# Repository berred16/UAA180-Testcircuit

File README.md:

# UAA180-Testcircuit
Cascading UAA180
Here you can find a drawing of the UAA180 Levelmeter in a single circuit as well as in cascading structure

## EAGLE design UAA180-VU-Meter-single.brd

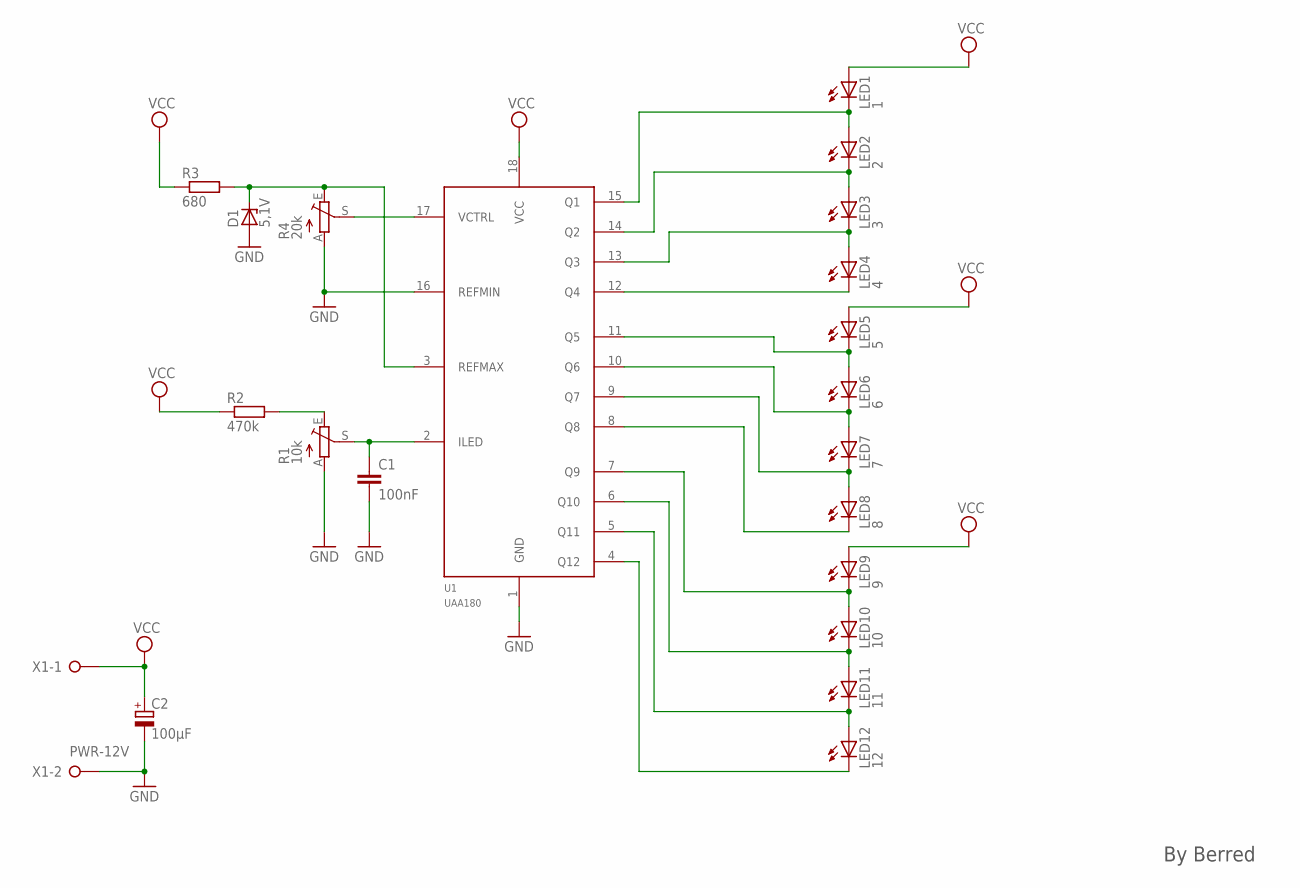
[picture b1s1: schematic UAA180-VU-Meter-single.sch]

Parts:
C1: 100nF; C025-024X044
C2: 100µF; E2,5-7
D1: 5,1V; DO35Z10
LED1: 1; LED2X5
LED2: 2; LED2X5
LED3: 3; LED2X5
LED4: 4; LED2X5
LED5: 5; LED2X5
LED6: 6; LED2X5
LED7: 7; LED2X5
LED8: 8; LED2X5
LED9: 9; LED2X5
LED10: 10; LED2X5
LED11: 11; LED2X5
LED12: 12; LED2X5
R1: 10k; B25P
R2: 470k; 0207/10
R3: 680; 0207/10
R4: 20k; B25P
U1: UAA180; DIL18
X1: PWR-12V; W237-132

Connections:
GND: C1.2, C2.-, D1.A, R1.A, R4.A, U1.1 (GND), U1.16 (REFMIN), X1.2
unnamed: LED1.K (C), LED2.A, U1.15 (Q1)
unnamed: LED2.K (C), LED3.A, U1.14 (Q2)
unnamed: LED3.K (C), LED4.A, U1.13 (Q3)
unnamed: LED4.K (C), U1.12 (Q4)
unnamed: LED5.K (C), LED6.A, U1.11 (Q5)
unnamed: LED6.K (C), LED7.A, U1.10 (Q6)
unnamed: LED7.K (C), LED8.A, U1.9 (Q7)
unnamed: R4.S, U1.17 (VCTRL)
unnamed: C1.1, R1.S, U1.2 (ILED)
unnamed: LED8.K (C), U1.8 (Q8)
unnamed: LED9.K (C), LED10.A, U1.7 (Q9)
unnamed: LED10.K (C), LED11.A, U1.6 (Q10)
unnamed: LED11.K (C), LED12.A, U1.5 (Q11)
unnamed: LED12.K (C), U1.4 (Q12)
unnamed: R1.E, R2.2
unnamed: D1.C, R3.2, R4.E, U1.3 (REFMAX)
VCC: C2.+, LED1.A, LED5.A, LED9.A, R2.1, R3.1, U1.18 (VCC), X1.1

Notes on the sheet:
By Berred

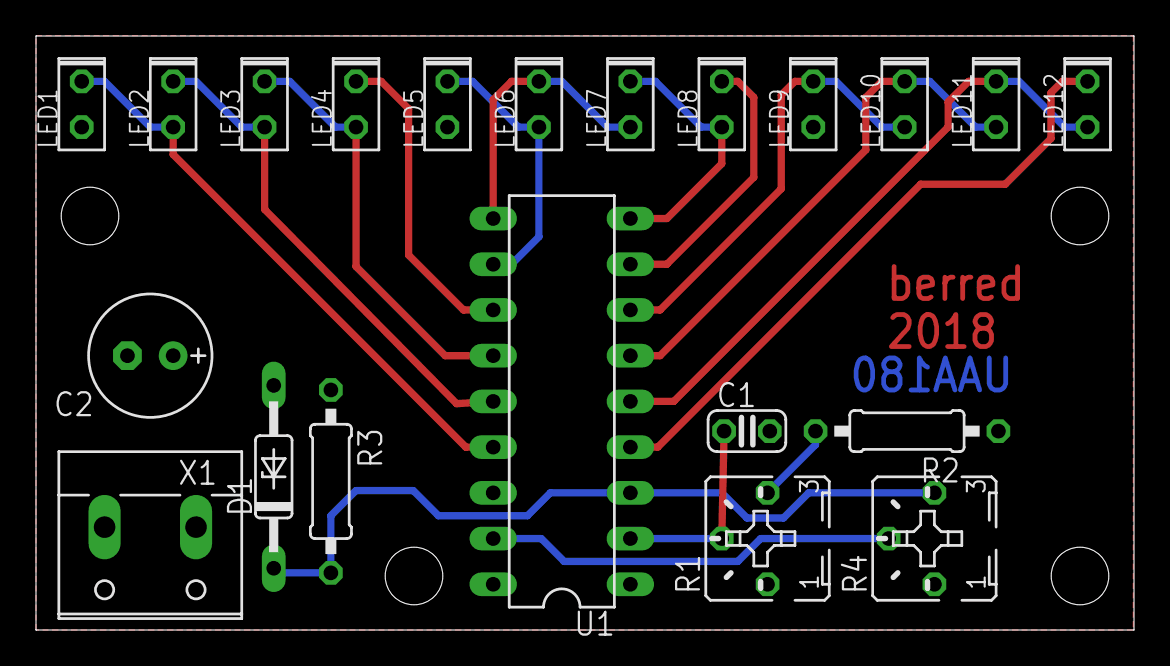
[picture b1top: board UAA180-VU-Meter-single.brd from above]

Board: 2 copper layers, 61.0 x 33.0 mm, 21 parts (0 on the bottom side), 18 nets.
